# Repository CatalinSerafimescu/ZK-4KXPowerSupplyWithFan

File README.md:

# ZK-4KX Enhanced Power Supply — temperature-controlled fan

A bench power supply built around the cheap **ZK-4KX buck-boost panel module** (IN 5–30 V, OUT 0.5–30 V,
[datasheet](https://www.laskakit.cz/user/related_files/zk-4kx_english.pdf)), with a 3D-printed case and a small
add-on board that runs a cooling fan **only when the module gets warm**, faster as it gets hotter.
Everything runs from the same DC input (9 V / 2 A adapter tested, up to ~28 V supported).

| Finished supply | Inside |
|---|---|
|  |  |

- Single-sided PCB, 90 × 66 mm, designed for **home etching** (toner transfer, no vias, no jumpers) — Gerbers included if you'd rather order it.
- Through-hole parts only: LM35, LM358, LM317, 78L05, one trimmer.
- Fan **off** below a start temperature you set with the trimmer (~15 … 52 °C), full speed ~18 °C above it.
- Fan voltage can never exceed 5 V, whatever the input voltage or faults.
- Printable case, 98 × 128 × 68 mm, magnetic lid, no supports.

**Build guide:** [instruction.md](instruction.md) — parts, etching, assembly, wiring, first power-up, calibration, troubleshooting.

## Downloads

| What | File |
|---|---|
| Bill of materials | [bom.md](bom.md) |
| Schematic | [KiCAD/SursaTensiune_sch.pdf](KiCAD/SursaTensiune_sch.pdf) |
| PCB print for toner transfer (+ solder mask film), A4, print at 100 % | [KiCAD/toner_B.Cu_1to1.pdf](KiCAD/toner_B.Cu_1to1.pdf) |
| Gerbers + drill files for ordering the PCB | [KiCAD/gerber/SursaTensiune_gerbers.zip](KiCAD/gerber/SursaTensiune_gerbers.zip) |
| Assembly BOM in PCBWay's format | [KiCAD/SursaTensiune_BOM_PCBWay.xlsx](KiCAD/SursaTensiune_BOM_PCBWay.xlsx) |
| Enclosure, printable | [Enclosure_base.3mf](mechanical/enclosure/Enclosure_base.3mf), [Enclosure_cover.3mf](mechanical/enclosure/Enclosure_cover.3mf) (print orientation; STL and STEP next to them), [Bambu Studio project for the A1](mechanical/enclosure/Enclosure_A1_project.3mf) — see [enclosure notes](mechanical/enclosure/README.md) |
| Solder-mask jig, printable (optional) | [Mask_jig.stl](mechanical/mask_jig/Mask_jig.stl) — see [jig notes](mechanical/mask_jig/README.md) |
| KiCad 10 project | [KiCAD/](KiCAD/) — see [PCB_info.md](KiCAD/PCB_info.md) |

## Build photos

| Design | | |
|---|---|---|
|  |  |  |
| PCB layout (KiCad) | 3D view | Enclosure (FreeCAD) |

| Making the board | | |
|---|---|---|
|  |  |  |
| Toner transferred | Etched | UV solder mask, board in the printed jig |
|  |  |  |
| Soldered (bottom) | Assembled board | Closed case, vents on top |

## How it works

| Block | Parts | Function |
|---|---|---|
| 5 V aux | U3 78L05, C3, C4, C5 | Supplies U2 and the LM35 |
| Start temperature | R1, RV1, R5, U2B | V_REF = 0 … 0.42 V, buffered |
| Amplifier | U4 LM35, U2A, R2, R3 | V_ADJ = 11·V_LM35 − 10·V_REF (clamped 0 … ~3.5 V by the 5 V supply) |
| Fan supply | U1 LM317, C1, C2, R4, D1 | V_FAN = V_ADJ + 1.25 V → 1.25 V (off) … 4.75 V (full) |

- Fan: Raspberry Pi type 30×30×10 mm, 5 V / 0.2 A, 2-wire. The LM35 sits on the ZK-4KX heatsink.
- Fan starts (≈ 2.8 V, measured) at **T_start**, reaches full speed at **T_start + ~18 °C**.
- T_start range with RV1: **~15 … 52 °C**.
- **Calibration:** measure U2 pin 7 → **V_REF [mV] = 11 · T_start − 155** (e.g. 285 mV → 40 °C).
- Narrower ramp (~9.5 °C): R2 = 5.1 kΩ.
- Fail-safes: pot wiper open → fan runs from ~17 °C (R5); LM35 disconnected → fan full speed.
- U1 dissipation: 0.9 W @ 9 V in, 5.3 W @ 30 V in (HS1 + insulating kit; tab = OUT).
- Simulated in both ngspice and LTspice (nominal, trimmer extremes, input sweep, power-up, open wiper/sensor,
  op-amp offset worst cases) — see [simulation/README.md](simulation/README.md).

## Repository layout

| Path | Content |
|---|---|
| `bom.py` → `bom.md` | BOM, single source of truth. Run `python bom.py`. |
| `instruction.md` | Build guide |
| `schematic/` | Schematic image (schemdraw, `gen_schematic.py`), labels from `bom.py` |
| `KiCAD/` | KiCad 10 project, generator scripts (`gen/`), print PDF, Gerbers. See `KiCAD/PCB_info.md`. |
| `simulation/` | Same scenarios in ngspice 46 and LTspice 26 |
| `mechanical/` | Enclosure and solder-mask jig (FreeCAD scripts, STEP, STL, 3MF), part models used for fit checks. See `mechanical/README.md`. |
| `photos/` | Build photos |

## Credits and third-party files

These files are not mine and keep their original terms (they are **not** covered by this project's licenses):

- `mechanical/stl/ZK-4KX Buck Boost Converter.STL` — by Legacy_Micro,
  [Printables 401707](https://www.printables.com/model/401707-basic-model-zk-4kx-buck-boost-converter), CC0.
- `mechanical/button/DS-431_square_push_button_red.step` — from
  [GrabCAD](https://grabcad.com/cads/files/da40e36f2500ba5d71d7cf6f930e5d73/original.step).
- `mechanical/fan/Fan_30x30x10_5V_2pin.step` — modified from A. Kirchner's 30×30×8 fan model,
  [GrabCAD](https://grabcad.com/library/fan-30x30x8mm-5v-2-pin-1).
- `mechanical/dc_jack/DC_jack_5.5x2.1_panel_10A.step` (+ 2 renders) — from
  [GrabCAD](https://grabcad.com/library/power-jack-socket-5-5-x-2-1-mm-10a-dc-1).
- `mechanical/heatsink/*.jpg` — TME product images of the Stonecold RAD-DY-KY heatsink.
- ZK-4KX datasheet and heatsink datasheet are linked, not included.

**Not included** (licences don't allow redistribution) — download them and save under these names if you need them:

| File | What | Where to get it | Needed for |
|---|---|---|---|
| `KiCAD/vendor/3386P-1-103LF.stp` | Bourns 3386P trimmer 3D model | [SamacSys / Component Search Engine](https://componentsearchengine.com) | RV1 3D body in KiCad |
| `mechanical/trimmer/3386P-1-103LF.stp` | same model (copy) | as above | reference only |
| `mechanical/banana/930176100.stp` | Hirschmann 930176100 banana socket | [SamacSys / Component Search Engine](https://componentsearchengine.com) | `mechanical/enclosure/assembly.py` |
| `simulation/vendor/onsemi_LM358.mod` | onsemi LM358 SPICE model | [onsemi models](https://onsemi.com/support/design-resources/models?rpn=LM358) | `run_sim.py --vendor` |
| `simulation/vendor/LT317A.sub` | ADI LT317A SPICE model | bundled with LTspice (`lib.zip` → `lib/sub/LT317A.sub`) | `run_sim.py --vendor` |

Everything else (schematic, PCB, Gerbers, enclosure, behavioral simulations) works without them.

## Support

If this project saved you some time, you can buy me a coffee (via PayPal):

## License

Copyright © 2026 Catalin Serafimescu. See [LICENSE](LICENSE):

- Hardware (KiCad project, Gerbers, enclosure and jig) — [CERN-OHL-S-2.0](LICENSES/CERN-OHL-S-2.0.txt)
- Software (Python scripts, SPICE files) — [MIT](LICENSES/MIT.txt)
- Documentation and images — [CC BY-SA 4.0](LICENSES/CC-BY-SA-4.0.txt)

Mains is not involved, but you are working with up to 30 V / 4 A — build and use at your own risk.

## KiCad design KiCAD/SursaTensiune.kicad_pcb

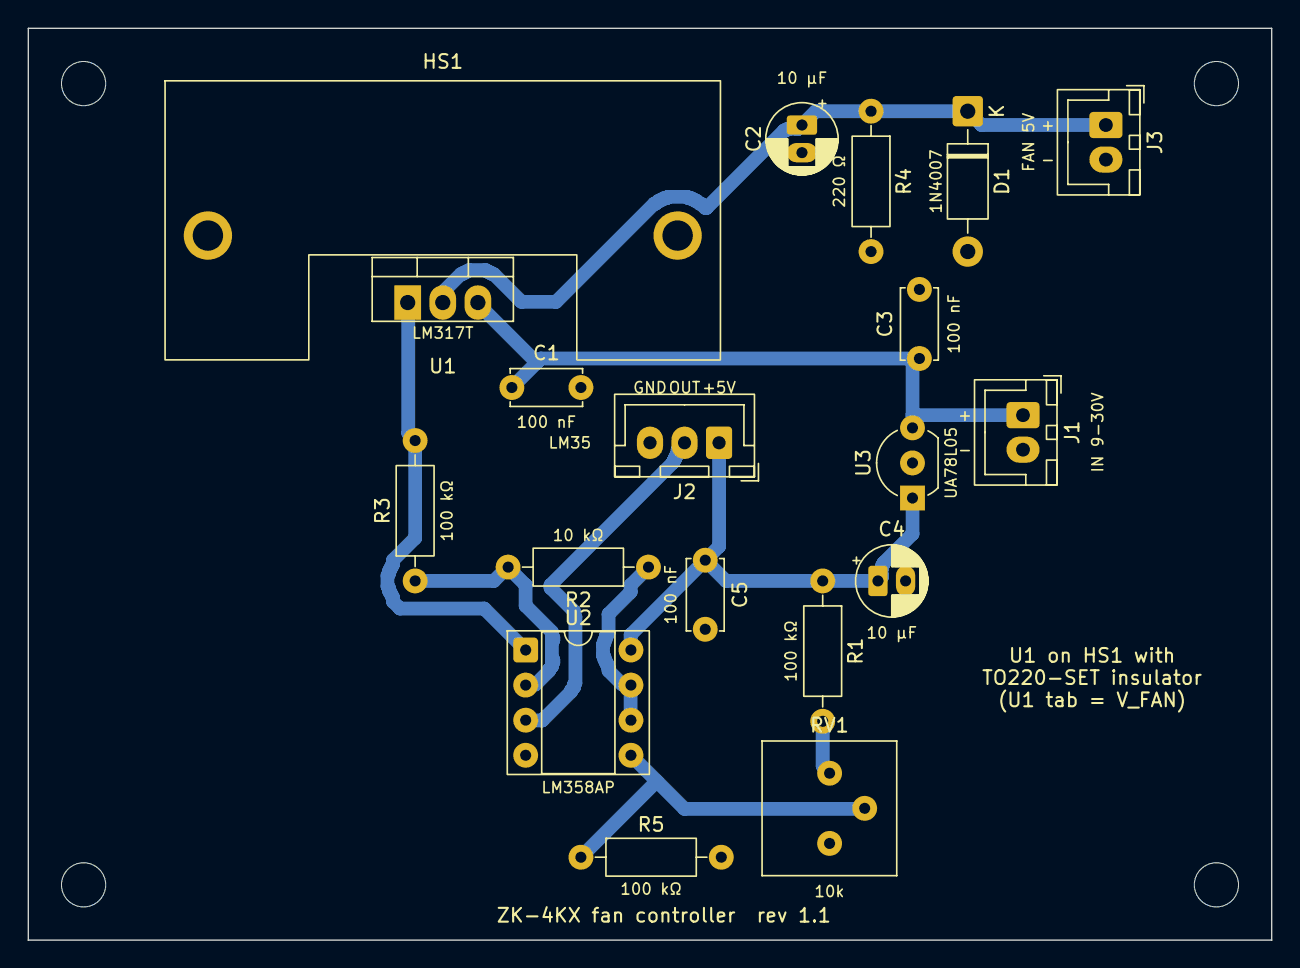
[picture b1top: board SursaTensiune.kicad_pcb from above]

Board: 2 copper layers, 90.0 x 66.0 mm, 23 parts (0 on the bottom side), 10 nets.

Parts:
C1, C3, C5: 100 nF; C_Disc_D5.0mm_W2.5mm_P5.00mm
C2, C4: 10 µF; CP_Radial_D5.0mm_P2.00mm
D1: 1N4007; D_DO-41_SOD81_P10.16mm_Horizontal
H1, H2, H3, H4: M3; MountingHole_3.2mm_M3
HS1: RAD-DY-KY/3; Heatsink_Stonecold_RAD-DY-KY-3_40x20mm_P34mm
J1: IN 9-30V; JST_XH_B2B-XH-A_1x02_P2.50mm_Vertical
J2: LM35; JST_XH_B3B-XH-A_1x03_P2.50mm_Vertical
J3: FAN 5V; JST_XH_B2B-XH-A_1x02_P2.50mm_Vertical
R1, R3, R5: 100 kΩ; R_Axial_DIN0207_L6.3mm_D2.5mm_P10.16mm_Horizontal
R2: 10 kΩ; R_Axial_DIN0207_L6.3mm_D2.5mm_P10.16mm_Horizontal
R4: 220 Ω; R_Axial_DIN0207_L6.3mm_D2.5mm_P10.16mm_Horizontal
RV1: 10k; Potentiometer_Bourns_3386P_Vertical
U1: LM317T; TO-220-3_Vertical
U2: LM358AP; DIP-8_W7.62mm_Socket
U3: UA78L05; TO-92_Inline_Wide

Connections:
/+5V: C4.1, C5.1, J2.1, R1.1, U2.8, U3.1
/GND: C1.2, C2.2, C3.2, C4.2, C5.2, D1.2, J1.2, J2.3, J3.2, R4.2, R5.2, RV1.1, U2.4, U3.2
/LM35_OUT: J2.2, U2.3
/N_INV: R2.2, R3.1, U2.2
/POT_TOP: R1.2, RV1.3
/VADJ: R3.2, U1.1, U2.1
/VFAN: C2.1, D1.1, J3.1, R4.1, U1.2
/VIN: C1.1, C3.1, J1.1, U1.3, U3.3
/VREF: R2.1, U2.6, U2.7
/WIPER: R5.1, RV1.2, U2.5

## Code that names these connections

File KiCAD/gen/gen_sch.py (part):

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
# Block B — board connectors + the off-board parts plugged into them
part("J1", "Connector:Conn_01x02_Pin", (111.76, 111.76), {"1": "VIN", "2": "GND"}, FP["XH2"])
part("J2", "Connector:Conn_01x03_Pin", (111.76, 129.54), {"1": "+5V", "2": "LM35_OUT", "3": "GND"}, FP["XH3"])
part("J3", "Connector:Conn_01x02_Pin", (111.76, 167.64), {"1": "VFAN", "2": "GND"}, FP["XH2"])
part("U4", "Sensor_Temperature:LM35-LP", (45.72, 129.54), {"1": "+5V", "2": "LM35_OUT", "3": "GND"})
part("M1", "Motor:Fan", (45.72, 167.64), {"1": "VFAN", "2": "GND"})

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    ((177.8, 213.36), "V_FAN = V_ADJ + 1.25 V  (1.25 … 4.75 V)", 1.5),
    ((27.94, 88.9), "J5: centre = + (check adapter).  Do NOT tie ZK-4KX OUT− to IN−.", 1.5),
    ((27.94, 190.5), "LM35 on the ZK-4KX rear heatsink (fin root). Check heatsink potential; insulate the legs.", 1.5),
    ((177.8, 162.56), "RV1 trimmer: pin 3 = POT_TOP → clockwise = higher start temperature.", 1.5),
    ((177.8, 238.76), "HS1: U1 on RAD-DY-KY/3 (2 PCB pins, M3) with TO220-SET insulator (U1 tab = V_FAN!).  "
                      "0.9 W @ 9 V in, 5.3 W @ 30 V in.", 1.5),
    ((27.94, 254.0), "Simulation: ../simulation (ngspice 46, 11 scenarios PASS).  BOM: ../bom.md "
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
